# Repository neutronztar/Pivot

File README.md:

# Pivot
Pivot is an open source robotic art piece similar to Mark Setrakian's [Axis 1 and 2](https://www.youtube.com/watch?v=NsFBHqbNKvA&t=72s). Here is [a video](https://youtu.be/PGe4sWHx0f0) about how I designed and built it

## Bill of Materials
### General Parts
| Part                                   | Quantity    | Approx Price   | Total | Notes |
|----------------------------------------|-------------|----------------|------|-------|
| [LX-16A Servo](https://smile.amazon.com/gp/product/B073XY5NT1/ref=ppx_yo_dt_b_search_asin_title?ie=UTF8&psc=1)    | 15          | $20            | $300 | You also need the wires and plastic mounting rings that come with these.
| [JoyStick](https://smile.amazon.com/dp/B08CGYGMJL?psc=1&ref=ppx_yo2_dt_b_product_details) | 1 | $21 | $21 |
| [2 x 0.4 x 8 mm Machine Screws](https://www.boltdepot.com/Metric_socket_cap_Class_12.9_alloy_steel_black_oxide_finish_2mm_x_0.4mm.aspx?Selected=13324) | 400 | $0.0946 | $38 | Exact qty is 300, but you should get some extra. |
| [12V Power Supply](https://www.ebay.com/itm/153588427332) | 1 | $7 | $7 |
| [AC Power Connector](https://smile.amazon.com/dp/B00H8QL53A?psc=1&ref=ppx_yo2_dt_b_product_details) | 1 | $7 | $7 |
| [PETG Filament](https://smile.amazon.com/gp/product/B07PGYHYV8/ref=ppx_yo_dt_b_search_asin_title?ie=UTF8&psc=1) | 1kg | $23 | $23 |  |
| [Plaster of Paris](https://smile.amazon.com/Dap-Plaster-Paris-20-Min/dp/B008SR3W1G/ref=sr_1_4?crid=1MEP5MWMSY1YV&keywords=plaster+of+paris&qid=1642203001&sprefix=plaster+of+paris%2Caps%2C111&sr=8-4) | 1 | $10 | $10 |  |
| [Round Power Switch](https://www.ebay.com/itm/203485577266?hash=item2f60af8032:g:Sh4AAOSwmDtgvNwT) | 1 | $3 | $3 |  |
| [Power Connector](https://smile.amazon.com/gp/product/B07DCXKNXQ/ref=ppx_yo_dt_b_search_asin_title?ie=UTF8&psc=1) | 1 | $7 | $7 |  |

### PCB Parts
| Part                                   | Quantity    | Approx Price   | Total | Notes |
|----------------------------------------|-------------|----------------|------|-------|
| [ESP32 DevKit](https://smile.amazon.com/gp/product/B086MLNH7N/ref=ppx_yo_dt_b_search_asin_title?ie=UTF8&psc=1)    | 1           | $7             | $7 |
| [8V Buck Converter](https://smile.amazon.com/dp/B07BDDMGLG?ref=ppx_yo2_dt_b_product_details&th=1) | 1 | $7 | $7 |
| [5V Buck Converter](https://smile.amazon.com/gp/product/B01MQGMOKI/ref=ppx_yo_dt_b_search_asin_title?ie=UTF8&th=1) | 1 | $11 | $11 |
| [Molex Spox 3pin Connectors](https://www.mouser.com/ProductDetail/Molex/35301-0340?qs=sGAEpiMZZMskC5GgilGuvsx2BO7CxsBR&countrycode=US&currencycode=USD) | 5 | $0.26 | $1.30 | |
| [1000uF Electrolytic Cap](https://smile.amazon.com/dp/B06XRDWF5X?psc=1&ref=ppx_yo2_dt_b_product_details) | 4 |  | $15 |  |
| [10uF Electrolytic Cap](https://smile.amazon.com/dp/B06XRDWF5X?psc=1&ref=ppx_yo2_dt_b_product_details) | 1 |   |  |  |
| [Tri-State Buffer: SN74LS241N](https://smile.amazon.com/gp/product/B08FZVPJD9/ref=ppx_yo_dt_b_search_asin_title?ie=UTF8&psc=1) | 1 | $9 | $9 |  |
| Logic Level Shifter SMD: TXS0108EPWR | 1 |   |  | JLC |
| 1k Resistor SMD: 0603WAF1001T5E | 1 |  |  | JLC |
| 10k Resistor SMD: 0603WAF1002T5E | 1 |  |  | JLC |
| 100nF Cap SMD: CC0603KRX7R9BB104 | 2 |  |  | JLC |

### 3D Printed Parts
| Part | Quantity |
|------|------|
| tip.STL | 5 |
| fingerA.STL | 5 |
| knuckle.STL | 5 |
| palm.STL | 1 |
| mid.STL | 1 |
| base.STL | 1 |

#### Approximate Grand Total: $466

## The Code
To make this machine do its magic, every ".py" file in the root of the "MicroPython" directory must be uploaded to the ESP32. I used the utility ["rshell"](https://pypi.org/project/rshell/) to do this. Also the ESP32 must first be loaded with a [MicroPython binary](https://micropython.org/download/esp32/) (tested on v1.17).

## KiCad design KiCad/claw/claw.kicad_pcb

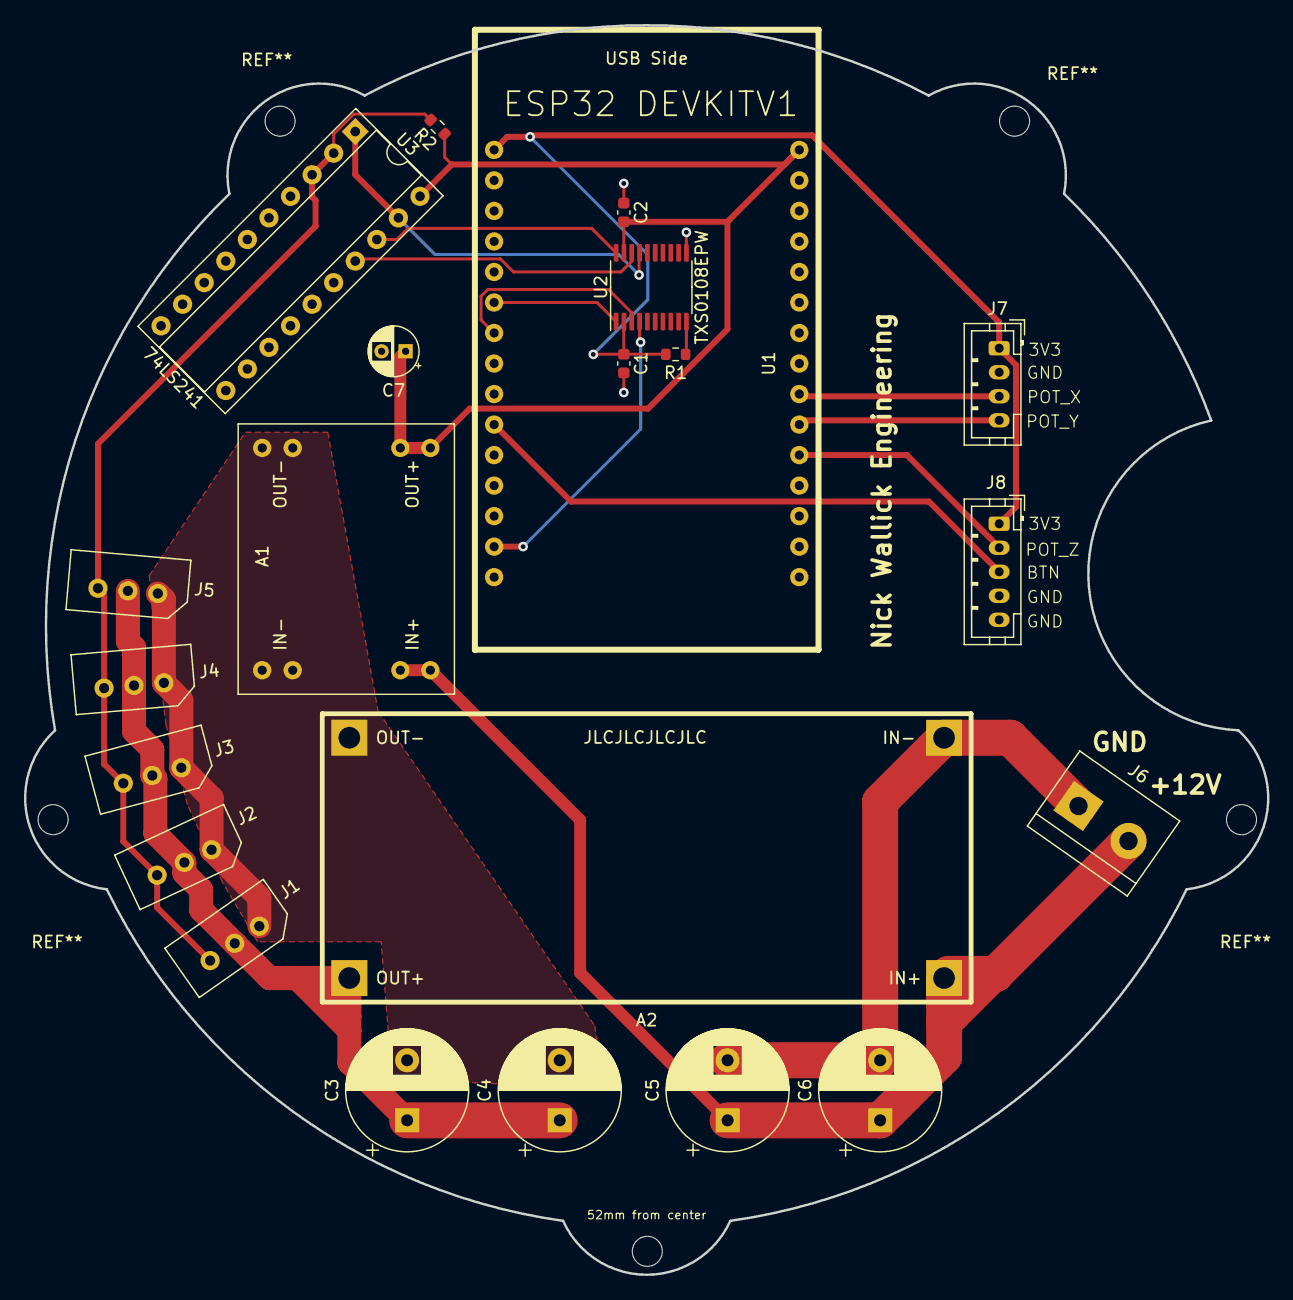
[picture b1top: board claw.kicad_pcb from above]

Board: 2 copper layers, 103.5 x 104.0 mm, 22 parts (0 on the bottom side), 17 nets.

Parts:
A1: DC-DC_Buck; MP1584EN_DC-DC_Buck
A2: DC-DC_Buck; DZS_Elec_DC-DC_Buck
C1, C2: 100nF; C_0603_1608Metric
C3, C4, C5, C6: 1000u; CP_Radial_D10.0mm_P5.00mm
C7: 10u; CP_Radial_D4.0mm_P2.00mm
J1, J2, J3, J4, J5: Molex_Spox_3pin; Molex_Spox_3Pin_2.5mmPitch
J6: Screw_Terminal_01x02; TerminalBlock_bornier-2_P5.08mm
J7: Conn_01x04_Male; JST_PH_B4B-PH-K_1x04_P2.00mm_Vertical
J8: Conn_01x05_Male; JST_PH_B5B-PH-K_1x05_P2.00mm_Vertical
R1: 1k; R_0603_1608Metric
R2: 10k; R_0603_1608Metric
U1: ESP32_DEVKITV1
U2: TXS0108EPW; TSSOP-20_4.4x6.5mm_P0.65mm
U3: 74LS241; DIP-20_W7.62mm_Socket

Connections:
+3V3: C1.1, J7.1, J8.1, R1.1, U1.1, U2.2
+5V: A1.3, C2.2, C7.1, R2.1, U1.30, U2.19, U3.20
+8V: A2.3, C3.1, C4.1, J1.2, J2.2, J3.2, J4.2, J5.2
+12V: A1.4, A2.4, C5.1, C6.1, J6.2
BUTTON: J8.3, U1.10
DIR_3V3: U1.14, U2.4
DIR_5V: U2.17, U3.1, U3.19
GND: A1.1, A1.2, A2.1, A2.2, C1.2, C2.1, C3.2, C4.2, C5.2, C6.2, C7.2, J1.1, J2.1, J3.1, J4.1, J5.1, J6.1, J7.2, J8.4, J8.5, U1.2, U1.29, U2.11, U3.10
MOTOR_SIGNAL: J1.3, J2.3, J3.3, J4.3, J5.3, R2.2, U3.2, U3.3
unnamed: R1.2, U2.10
POT_X: J7.3, U1.22
POT_Y: J7.4, U1.21
POT_Z: J8.2, U1.20
RX_3V3: U1.6, U2.1
RX_5V: U2.20, U3.18
TX_3V3: U1.7, U2.3
TX_5V: U2.18, U3.17

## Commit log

2021-09-20 Update README.md
    first
2021-09-20 poopoo
2021-09-20 test file
2021-09-20 message
2021-09-20 added knuckle.stl
2021-09-20 added motor step and knuckle step
2021-09-20 added palm
2021-09-21 created palm prototype and messed around with assemblies
2021-09-21 added freecad practice folder
2021-09-22 fixed problem connecting palm to servos in assembly4
2021-09-23 started natural version of palm and added sliced folder
2021-09-28 worked on fingerA
2021-11-13 did some things
2021-11-13 added .gitignore
2021-11-18 created test files for controlling motors
2021-11-19 started 3d motor angle calculation
2021-11-20 completed calc_angles() and added timeit()
2021-11-25 set offsets for all fingers and restructured functions to be in claw object
2021-11-25 no more .vscode
2021-11-25 no more .vscode/
2021-11-25 ignore .vscode/*
2021-11-25 trying to ignore .vscode
2021-11-26 added validate() for validating results from servos
2021-11-27 restructured lx16.py and added query_motors() to claw.py
2021-12-01 ignored __pycache__
2021-12-04 changed form-factor to "starfish"
2021-12-04 added files for reading rotary encoders
2021-12-04 moved main loop to "main.py" and kept supporting functins in "claw.py"
2021-12-05 added 5 attempts each to read functions
2021-12-05 added radius knob
2021-12-05 sprinkled const() on some variables
2021-12-16 added new sliced files
2021-12-16 ditched rotary encoders and added joystick control
2021-12-16 added joystick radius and speed control
2021-12-17 cleaned up repo and added KiCAD circuitboard data
2021-12-17 Drop files from .gitignore
2021-12-18 added joystick connectors to schematic and layed out components on pcb
2021-12-18 pcb traces
2021-12-18 added PCB mounting holes
2022-01-09 updated finger offsets
2022-01-10 updated notes
2022-01-10 added all 3D models
2022-01-12 started BOM
2022-01-14 made plot for video
2022-01-14 updated BOM and added /media
2022-01-15 updated documentation a bit
2022-01-15 changed image
2022-01-15 lx16.py description
2022-01-15 test name change
2022-01-15 added video link
2022-01-20 updated media with more pics
2022-01-22 kicad update
2022-01-22 added license
2022-01-22 added license to lx16.py
2022-02-26 updated "installing micropython" directions
2022-03-06 updated SLOP constant
